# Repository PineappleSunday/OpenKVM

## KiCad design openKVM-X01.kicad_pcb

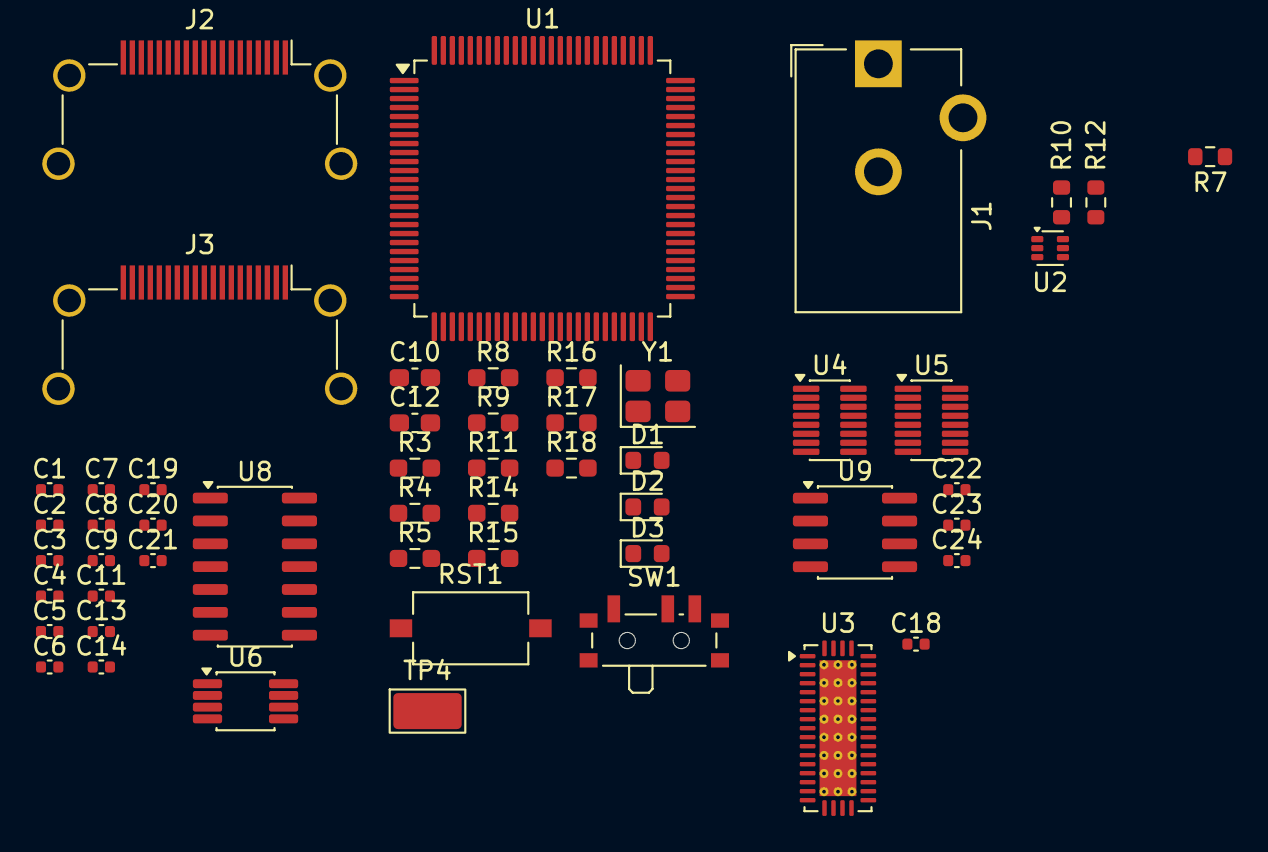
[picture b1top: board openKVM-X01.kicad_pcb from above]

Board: 2 copper layers, 53 parts (0 on the bottom side), 57 nets, no tracks yet.

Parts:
C1, C2, C3, C4, C6, C7, C9, C13, C18, C19, C20, C21, C22, C23, C24: 100nF; C_0402_1005Metric
C5, C8: 10pF; C_0402_1005Metric
C10, C12: 2uF2; C_0603_1608Metric_Pad1.08x0.95mm_HandSolder
C11: 2uF2; C_0402_1005Metric
C14: 470nF; C_0402_1005Metric
D1: GRN LED; LED_0603_1608Metric
D2: RED LED; LED_0603_1608Metric
D3: BLU LED; LED_0603_1608Metric
J1: PJ-102AH; BarrelJack_CUI_PJ-102AH_Horizontal
J2, J3: HDMI_A_1.4; HDMI_A_Amphenol_10029449-x01xLF_Horizontal
R3, R4, R5: 500; R_0603_1608Metric_Pad0.98x0.95mm_HandSolder
R7: 10k; R_0603_1608Metric
R8, R9, R16: 10K; R_0603_1608Metric_Pad0.98x0.95mm_HandSolder
R10, R12: R; R_0603_1608Metric
R11: 33; R_0603_1608Metric_Pad0.98x0.95mm_HandSolder
R14, R15: 5K; R_0603_1608Metric_Pad0.98x0.95mm_HandSolder
R17, R18: 2K; R_0603_1608Metric_Pad0.98x0.95mm_HandSolder
RST1: SW_Push; SW_Tactile_SPST_NO_Straight_CK_PTS636Sx25SMTRLFS
SW1: SW_SPDT; SW_SPDT_PCM12
TP4: TestPoint; TestPoint_Keystone_5019_Miniature
U1: STM32F411VETx; LQFP-100_14x14mm_P0.5mm
U2: TPS562242B; SOT-563
U3: TS3DV642A0RUAR; WQFN-42-1EP_3.5x9mm_P0.5mm_EP2.05x7.55mm_ThermalVias
U4, U5: TMUX1574DYY; Texas_DYY0016A_TSOT-23-16_2x4.2mm_P0.5mm
U6: TCA9517ADGK; VSSOP-8_3x3mm_P0.65mm
U8: 74HC7014; SOIC-14_3.9x8.7mm_P1.27mm
U9: M24C02-RMN; SOIC-8_3.9x4.9mm_P1.27mm
Y1: Crystal; Crystal_SMD_3225-4Pin_3.2x2.5mm

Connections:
3V3: C22.1, C23.1, U4.16 (VDD), U5.16 (VDD)
5V: C21.1, C24.1, R17.2, R18.2, U6.8 (VCCB), U9.8 (VCC)
+3V3: C1.1, C3.1, C4.1, C6.1, C7.1, C9.1, C11.1, C13.1, C18.1, C19.1, C20.1, R8.2, R14.2, R15.2, SW1.1 (A), U1.6 (VBAT), U1.11 (VDD), U1.19 (VDD), U1.21 (VREF+), U1.22 (VDDA), U1.28 (VDD), U1.50 (VDD), U1.75 (VDD), U1.100 (VDD), U3.1 (VCC), U6.1 (VCCA)
+5V: J2.18 (+5V), J3.18 (+5V)
+12V: R7.1, U2.1 (VIN)
/ProjectArchitecture/HDMI/BOOT0: R9.2, TP4.1 (1_1), U1.94 (BOOT0)
/ProjectArchitecture/HDMI/EDID_EMULATION/5V_uC_I2C1_SCL: R17.1, U5.6 (S2B), U6.7 (SCLB)
/ProjectArchitecture/HDMI/EDID_EMULATION/5V_uC_I2C1_SDA: R18.1, U5.3 (S1B), U6.6 (SDAB)
/ProjectArchitecture/HDMI/EDID_EMULATION/COM1_EDID_EMU_SCL: U4.6 (S2B), U5.5 (S2A)
/ProjectArchitecture/HDMI/EDID_EMULATION/COM1_EDID_EMU_SDA: U4.3 (S1B), U5.2 (S1A)
/ProjectArchitecture/HDMI/HDMI_1_CEC: J2.13 (CEC), U3.18 (CEC_A)
/ProjectArchitecture/HDMI/HDMI_1_CK+: J2.10 (CK+), U3.32 (D3+A)
/ProjectArchitecture/HDMI/HDMI_1_CK-: J2.12 (CK-), U3.31 (D3-A)
/ProjectArchitecture/HDMI/HDMI_1_D0+: J2.7 (D0+), U3.38 (D0+A)
/ProjectArchitecture/HDMI/HDMI_1_D0-: J2.9 (D0-), U3.37 (D0-A)
/ProjectArchitecture/HDMI/HDMI_1_D1+: J2.4 (D1+), U3.36 (D1+A)
/ProjectArchitecture/HDMI/HDMI_1_D1-: J2.6 (D1-), U3.35 (D1-A)
/ProjectArchitecture/HDMI/HDMI_1_D2+: J2.1 (D2+), U3.34 (D2+A)
/ProjectArchitecture/HDMI/HDMI_1_D2-: J2.3 (D2-), U3.33 (D2-A)
/ProjectArchitecture/HDMI/HDMI_1_HPD: J2.19 (HPD/HEAC-), U3.19 (HPD_A)
/ProjectArchitecture/HDMI/HDMI_1_OUT_CK-: J3.12 (CK-), U3.13 (D3-)
/ProjectArchitecture/HDMI/HDMI_1_OUT_Ck+: J3.10 (CK+), U3.12 (D3+)
/ProjectArchitecture/HDMI/HDMI_1_OUT_D0+: J3.7 (D0+), U3.5 (D0+)
/ProjectArchitecture/HDMI/HDMI_1_OUT_D0-: J3.9 (D0-), U3.6 (D0-)
/ProjectArchitecture/HDMI/HDMI_1_OUT_D1+: J3.4 (D1+), U3.7 (D1+)
/ProjectArchitecture/HDMI/HDMI_1_OUT_D1-: J3.6 (D1-), U3.8 (D1-)
/ProjectArchitecture/HDMI/HDMI_1_OUT_D2+: J3.1 (D2+), U3.10 (D2+)
/ProjectArchitecture/HDMI/HDMI_1_OUT_D2-: J3.3 (D2-), U3.11 (D2-)
/ProjectArchitecture/HDMI/HDMI_1_OUT_SCK: J3.15 (SCL), U4.5 (S2A)
/ProjectArchitecture/HDMI/HDMI_1_OUT_SDA: J3.16 (SDA), U4.2 (S1A)
/ProjectArchitecture/HDMI/HDMI_1_SCK: J2.15 (SCL), U4.7 (D2)
/ProjectArchitecture/HDMI/HDMI_1_SDA: J2.16 (SDA), U4.4 (D1)
/ProjectArchitecture/HDMI/HDMI_COM_SEL: U1.15 (PC0), U4.1 (SEL)
/ProjectArchitecture/HDMI/HDMI_COM_SELECT: R11.2, U3.17 (SEL2)
/ProjectArchitecture/HDMI/HDMI_MUX_EN: U1.16 (PC1), U4.15 (~EN)
/ProjectArchitecture/HDMI/HDMI_TCA_EN: R16.2, U1.17 (PC2), U6.5 (EN)
/ProjectArchitecture/HDMI/MCU_OSC_IN: C5.1, U1.12 (RCC_OSC_IN), Y1.2
/ProjectArchitecture/HDMI/MCU_OSC_OUT: C8.1, U1.13 (RCC_OSC_OUT), Y1.1
/ProjectArchitecture/HDMI/NRST: C2.1, R8.1, RST1.2, U1.14 (NRST)
/ProjectArchitecture/HDMI/uC_I2C1_SCL: R14.1, U1.92 (I2C1_SCL), U6.2 (SCLA)
/ProjectArchitecture/HDMI/uC_I2C1_SDA: R15.1, U1.93 (I2C1_SDA), U6.3 (SDAA)
/ProjectArchitecture/POWER/U2_EN: R7.2, U2.5 (EN)
/ProjectArchitecture/POWER/U2_FB: R10.2, R12.1, U2.6 (FB)
BLU LED: R5.2, U1.40 (PE9)
GND: C1.2, C2.2, C3.2, C4.2, C5.2, C6.2, C7.2, C8.2, C9.2, C10.2, C11.2, C12.2, C13.2, C14.2, C18.2, C19.2, C20.2, C21.2, C22.2, C23.2, C24.2, D1.1 (K), D2.1 (K), D3.1 (K), J1.2, J2.2 (D2S), J2.5 (D1S), J2.8 (D0S), J2.11 (CKS), J2.17 (GND), J2.SH, J3.2 (D2S), J3.5 (D1S), J3.8 (D0S), J3.11 (CKS), J3.17 (GND), J3.SH, R12.2, R16.1, RST1.1, SW1.3 (C), U1.10 (VSS), U1.20 (VSSA), U1.27 (VSS), U1.49 (VSS), U1.74 (VSS), U1.99 (VSS), U2.3 (GND), U3.43 (EXP_GND), U4.8 (GND), U5.8 (GND), U6.4 (GND), U9.4 (VSS)
GRN LED: R3.2, U1.38 (PE7)
unnamed: C14.1, U8.1
unnamed: D1.2 (A), R3.1
unnamed: D2.2 (A), R4.1
unnamed: D3.2 (A), R5.1
unnamed: R9.1, SW1.2 (B)
unnamed: R11.1, U1.82 (PD1)
unnamed: C10.1, U1.48 (VCAP1)
unnamed: C12.1, U1.73 (VCAP2)
unnamed: U5.4 (D1), U9.5 (SDA)
unnamed: U5.7 (D2), U9.6 (SCL)
RED LED: R4.2, U1.39 (PE8)
